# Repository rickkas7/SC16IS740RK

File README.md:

# SC16IS740RK

*Interface to SC16IS740 UART for Particle devices*

It is recommended that you use 
[https://github.com/rickkas7/SC16IS7xxRK](https://github.com/rickkas7/SC16IS7xxRK)
which is an updated version of this library, instead. The new SC16IS7xxRK library supports 
dual-port chips, hardware flow control, and other options.

- Project Location: https://github.com/rickkas7/SC16IS740RK
- License: MIT. You can use this library without fee in open and closed-source projects. 

Sometimes you need more serial ports (UARTs) than are provided on the Particle Photon and Electron. One handy technique is to use an external I2C/SPI UART, such as the NXP SC16IS740.

This version supports I2C and SPI, but does not support hardware or software flow control or interrupts. Other features will be added later.

This library is also compatible with the mesh devices: Argon, Boron, and Xenon.

One difficulty is that the chip is only available in surface mount packages such as the TSSOP16. You'll need to use a [TSSOP-16 breakout board](https://www.adafruit.com/product/1207), make your own board (as described below) or put it directly on your own circuit board. As the pins are very small you may find it difficult to hand solder; it really should be mounted using a reflow oven.

You can connect up to 4 separate SC16IS740 chips to the single I2C interface on D0 and D1 by I2C.

The number of separate chips for SPI is limited to the number of available GPIO pins, as each one must have a unique CS pin, but they can share a single SPI bus.

When using a 1.8432 MHz oscillator it supports baud rate from 50 to 115200.

Note that the default I2C speed is 100 KHz, so it will be impossible to read or write continuously at 115200, but bursts that fit within the size of the FIFO (64 bytes) are fine.

Also, you can increase the speed of the I2C bus if all of the I2C devices support high speed mode by adding:

```
Wire.setSpeed(CLOCK_SPEED_400KHZ);
```

## Using the library

Include the SC16IS740RK library in your project and use it as follows:

```
#include "SC16IS740RK.h"

// Pick a debug level from one of these two:
SerialLogHandler logHandler;
// SerialLogHandler logHandler(LOG_LEVEL_TRACE);

SC16IS740 extSerial(Wire, 0);

char out = ' ';

void setup() {
	Serial.begin(9600);

	delay(5000);

	extSerial.begin(9600);
}

void loop() {
	while(extSerial.available()) {
		int c = extSerial.read();
		Log.info("received %d", c);
	}

	extSerial.print(out);
	if (++out >= 127) {
		out = ' ';
	}
	delay(100);
}
```

```
SC16IS740 extSerial(Wire, 0);
```

This initializes an SC16IS740 object as a global variable. The second parameter is the address set on the A0 and A1 pins. 

```
	extSerial.begin(9600);
```

Call begin() in setup() to set the baud rate. You can also set the number of data bits, parity, and stop bits.

The SC16IS740 library derives from Stream so the standard Arduino features like print, println, readUntil, etc. all work with this library.

## API

#### `public  `[`SC16IS740`](#class_s_c16_i_s740_1a48a15f05e738b52cca9549046b6360c5)`(TwoWire & wire,int addr,int intPin)` 

Construct the UART object. Typically done as a global variable.

#### Parameters
* `wire` The I2C port to use, typically Wire.

* `addr` The address you've set using the A0 and A1 pins, 0-3. This will be converted to the appropriate I2C address. Or you can directly specify the actual I2C address 0-127.

* `intPin` The interrupt pin (-1 = not used). Note: interrupts are not currently supported.

#### `public inline `[`SC16IS740`](#class_s_c16_i_s740)` & `[`withOscillatorHz`](#class_s_c16_i_s740_1a2bade8e74f73cd4175b295d7f6e620ce)`(int value)` 

Set the oscillator frequency in Hz (default: 1843200)

You must call this before begin.

#### `public void `[`begin`](#class_s_c16_i_s740_1a2914d7b2eb94a0d9413c295611814cd2)`(int baudRate,uint8_t options)` 

Set up the chip. You must do this before reading or writing.

#### Parameters
* `baudRate` the baud rate (see below)

* `options` The number of data bits, parity, and stop bits

You can call begin more than once if you want to change the baud rate. The FIFOs are cleared when you call begin.

Available baud rates depend on your oscillator, but with a 1.8432 MHz oscillator, the following are supported: 50, 75, 110, 134.5, 150, 300, 600, 1200, 1800, 2000, 2400, 3600, 4800, 7200, 9600, 19200, 38400, 57600, 115200

The valid options in standard number of bits; none=N, even=E, odd=O; number of stop bits format: OPTIONS\_8N1, OPTIONS\_8E1, OPTIONS\_8O1 OPTIONS\_8N2, OPTIONS\_8E2, OPTIONS\_8O2 OPTIONS\_7N1, OPTIONS\_7E1, OPTIONS\_7O1 OPTIONS\_7N2, OPTIONS\_7E2, OPTIONS\_7O2

#### `public inline void `[`blockOnOverrun`](#class_s_c16_i_s740_1a146f0afeb2d5efe71d2c44285a8260dd)`(bool value)` 

Defines what should happen when calls to [write()](#class_s_c16_i_s740_1ae95bfe10661800710fb0c3ed399dd6da)/print()/println()/printlnf() that would overrun the buffer.

blockOnOverrun(true) - this is the default setting. When there is no room in the buffer for the data to be written, the program waits/blocks until there is room. This avoids buffer overrun, where data that has not yet been sent over serial is overwritten by new data. Use this option for increased data integrity at the cost of slowing down realtime code execution when lots of serial data is sent at once.

blockOnOverrun(false) - when there is no room in the buffer for data to be written, the data is written anyway, causing the new data to replace the old data. This option is provided when performance is more important than data integrity.

## Test Circuit

In this circuit, I made the following connections:

- 1 VCC to 3V3 (red)
- 2 SCL to D1 (blue)
- 3 SDA to D0 (green)
- 4 <IRQ Can leave unconnected (not currently used) (white)
- 5 GND to GND (black)
- 6 >RST Can leave unconnected (red)
- 7 >RX to TX (yellow)
- 8 <TX to RX (orange)

Remember in serial you typically connect TX to RX and vice-versa. 

Also note that the serial is 3.3V logic level. You'll need a driver to connect it to a real RS232C device using +/- 12V signals!

The SC16IS740 is 5V tolerant on RX, however only when powered! If you can run into a case where the SC16IS740 is not powered, you can only supply 3.8V to RX. 

## Custom breakout board

I've included the Eagle CAD files for the breakout board I used above. 

- 1x 0.1 uF capacitor 0603
- 6x 10K ohm resistor 0603
- 1x [1.8432 MHz oscillator](https://www.digikey.com/product-detail/en/avx-corp-kyocera-corp/KC3225K1.84320C1GE00/1253-1488-1-ND/5322590) $1.36
- 1x [SC16IS740 UART](https://www.digikey.com/product-detail/en/nxp-usa-inc/SC16IS740IPW,112/568-3648-5-ND/1154236) $2.80

The holes marked A0 and A1 are designed for standard breakaway 0.1" header pins. The addresses have pull-downs on them so the default is 0, but if you install the header pins and a jumper, they'll be pulled high so you can set address 0 - 3.

## SPI Mode

In most cases, you'll save GPIO pins by using I2C. However, if you need the fastest speed possible, such as if you want multiple 115200 data streams, or if you want to do 230400 baud, you'll want to use SPI.

For the primary SPI (SPI):

| Name | Flash Alt Name | Particle Pin | Example Color |
| ---- | -------------- | ------------ | ------------- |
| SS   | CS             | A2           | White         |
| SCK  | CLK            | A3           | Orange        |
| MISO | DO             | A4           | Blue          |
| MOSI | DI             | A5           | Green         |

Instead of instantiating a SC16IS740 object, use the SC16IS740SPI object:

```
SC16IS740SPI extSerial(SPI, A2);
```

For the secondary SPI (SPI1):

| Name | Flash Alt Name | Particle Pin | Example Color |
| ---- | -------------- | ------------ | ------------- |
| SS   | CS             | D5           | White         |
| SCK  | CLK            | D4           | Orange        |
| MISO | DO             | D3           | Blue          |
| MOSI | DI             | D2           | Green         |

Instead of instantiating a SC16IS740 object, use the SC16IS740SPI object:

```
SC16IS740SPI extSerial(SPI1, D5);
```

## Version History

### 0.9.8 (2025-02-14)

- The fix in 0.0.3 added in 0.0.3 no longer works because `HAL_PLATFORM_MESH` is no longer defined; fixed again.

### 0.0.8 (2023-08-20)

- Recommendation to use SC16IS7xxRK instead.

### 0.0.7 (2020-05-04)

- Fix compiler error for undefined conversion to SpiClass with 1.5.1-rc.1.

### 0.0.6

- Fix compiler error for ambiguous requestFrom with 1.5.0-rc.2.

### 0.0.3

On mesh devices, temporarily disable SPI DMA as this causes a SOS fault on multi-byte read or write operations when using SPI.

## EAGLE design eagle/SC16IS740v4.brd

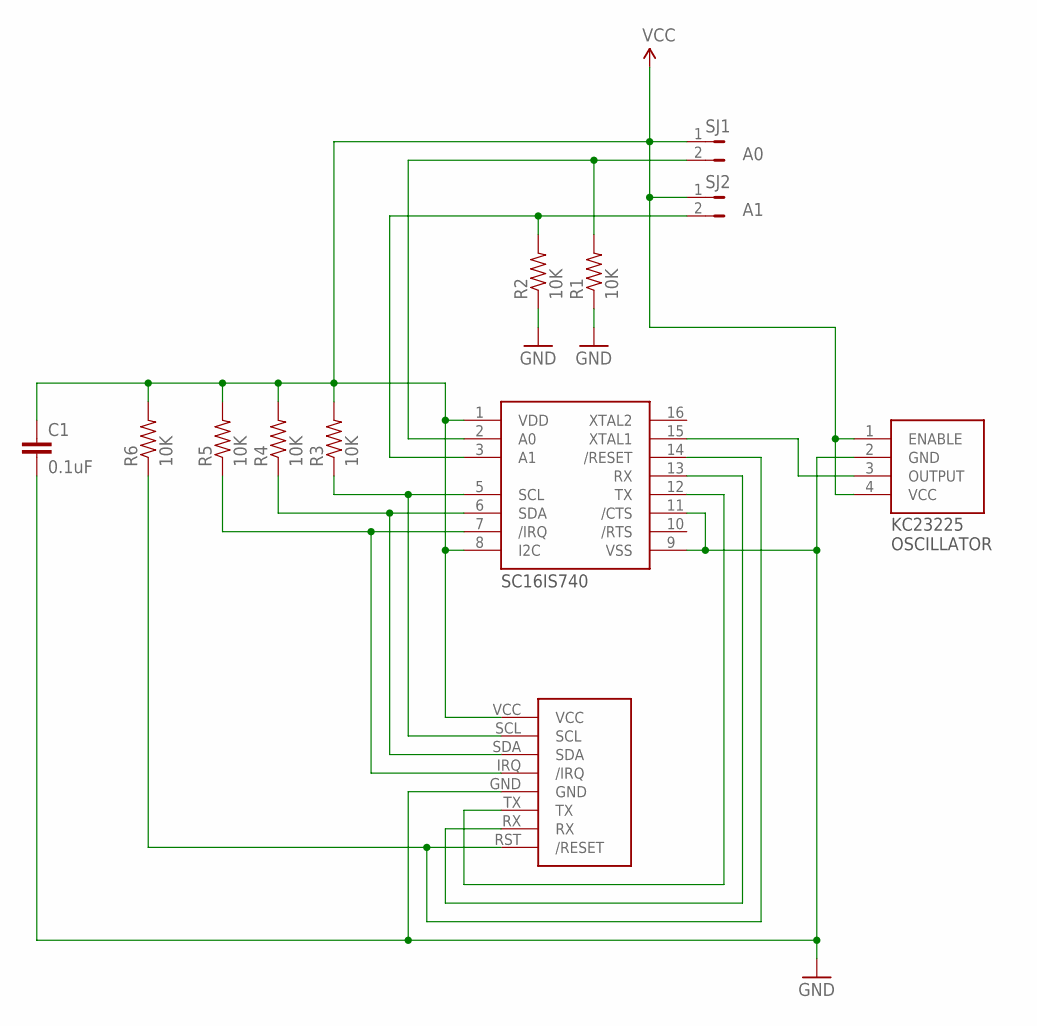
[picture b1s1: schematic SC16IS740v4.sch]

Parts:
C1: 0.1uF; 0603-CAP
R1, R2, R3, R4, R5, R6: 10K; 0603-RES
SJ1, SJ2: JUMPER-PTH-2-NO; PTH-JUMPER-2-NO_NO_SILK
U$1: SC16IS740
U$2: HEADER-SC16IS740-NOFLOW
U$3: OSC-KC3225K

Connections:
/IRQ: R5.1, U$1.7 (/IRQ), U$2.IRQ (/IRQ)
/RESET: R6.1, U$1.14 (/RESET), U$2.RST (/RESET)
A0: R1.2, SJ1.2, U$1.2 (A0)
A1: R2.2, SJ2.2, U$1.3 (A1)
GND: C1.2, R1.1, R2.1, U$1.9 (VSS), U$1.11 (/CTS), U$2.GND, U$3.2 (GND)
unnamed: U$1.15 (XTAL1), U$3.3 (OUTPUT)
RX: U$1.13 (RX), U$2.RX
SCL: R3.1, U$1.5 (SCL), U$2.SCL
SDA: R4.1, U$1.6 (SDA), U$2.SDA
TX: U$1.12 (TX), U$2.TX
VCC: C1.1, R3.2, R4.2, R5.2, R6.2, SJ1.1, SJ2.1, U$1.1 (VDD), U$1.8 (I2C), U$2.VCC, U$3.1 (ENABLE), U$3.4 (VCC)

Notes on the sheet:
KC23225 OSCILLATOR
SC16IS740

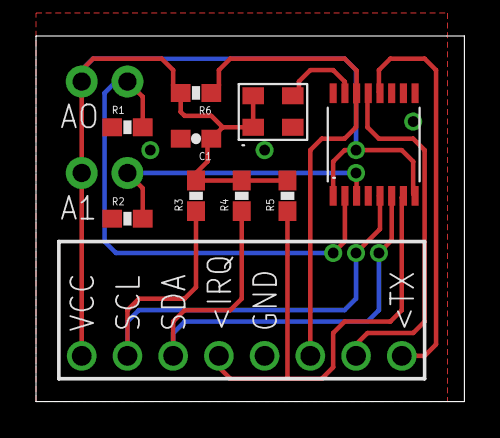
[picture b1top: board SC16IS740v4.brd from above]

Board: 2 copper layers, 23.8 x 20.3 mm, 12 parts (0 on the bottom side), 11 nets.

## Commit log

2018-06-14 initial checkin
2018-06-18 added info about limits of I2C speed
2018-06-18 checkpoint - not working yet
2018-06-22 checkpoint - sort of works, still not recommended
2018-06-22 block read and write calls work now!
2018-06-23 checkpoint - some self tests still fail
2018-06-23 Simple SPI works!
2018-07-03 travis support
2018-09-09 Version 0.0.2
    Fix implementation of peekByte()
2018-09-10 fix travis build
2018-11-24 Add note about compatibility with mesh
2019-02-01 Version 0.0.3
    - Fix SOS on mesh devices with multi-byte writesp
2019-02-21 Version 0.0.4
    - Make the Logger log statement static, otherwise it causes a SOS+1 fault on Device OS 1.0.0 due to to overwriting a conflicting declaration.
2020-03-10 Version 0.0.6
    - Fix compiler error for ambiguous requestFrom with 1.5.0-rc.2.
2020-05-05 Version 0.0.7
    - Fix compiler error for undefined conversion to SpiClass with 1.5.1-rc.1.
2021-02-23 Added link to API documentation
2022-04-12 Faster buffered writing in SC16IS740Base
    - Only write a maximum of half of the max available bytes at a time to improve writing frequency and decrease pauses between larger byte chunks
2022-04-12 Fix peekByte casting to uint8_t
    - Changed peekByte to an int8_t
    - Change hasPeek flag only if peekByte isnt -1
2022-06-28 Replaced SPI transfer mesh define check with DMA only from RAM check, the check did not work on b5som modules, as they are not mesh
2022-06-28 Added automatic driving of the RTS pin for RS485 communication, sets the pin polarity correctly for a MAX485 chip too
2022-06-28 Added multi channel support for ICs like the SC16IS752
2022-06-28 Updated README.md, updated changelog at the end
2022-06-28 Increased library version to 0.0.8
2023-08-20 0.0.8
    - Recommendation to use SC16IS7xxRK instead
2025-02-14 Version 0.0.9
    Fix problem with SPI on Gen 3

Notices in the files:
parts and their libraries:
SparkFun-Capacitors: Licensing: Creative Commons ShareAlike 4.0 International - https://creativecommons.org/licenses/by-sa/4.0
